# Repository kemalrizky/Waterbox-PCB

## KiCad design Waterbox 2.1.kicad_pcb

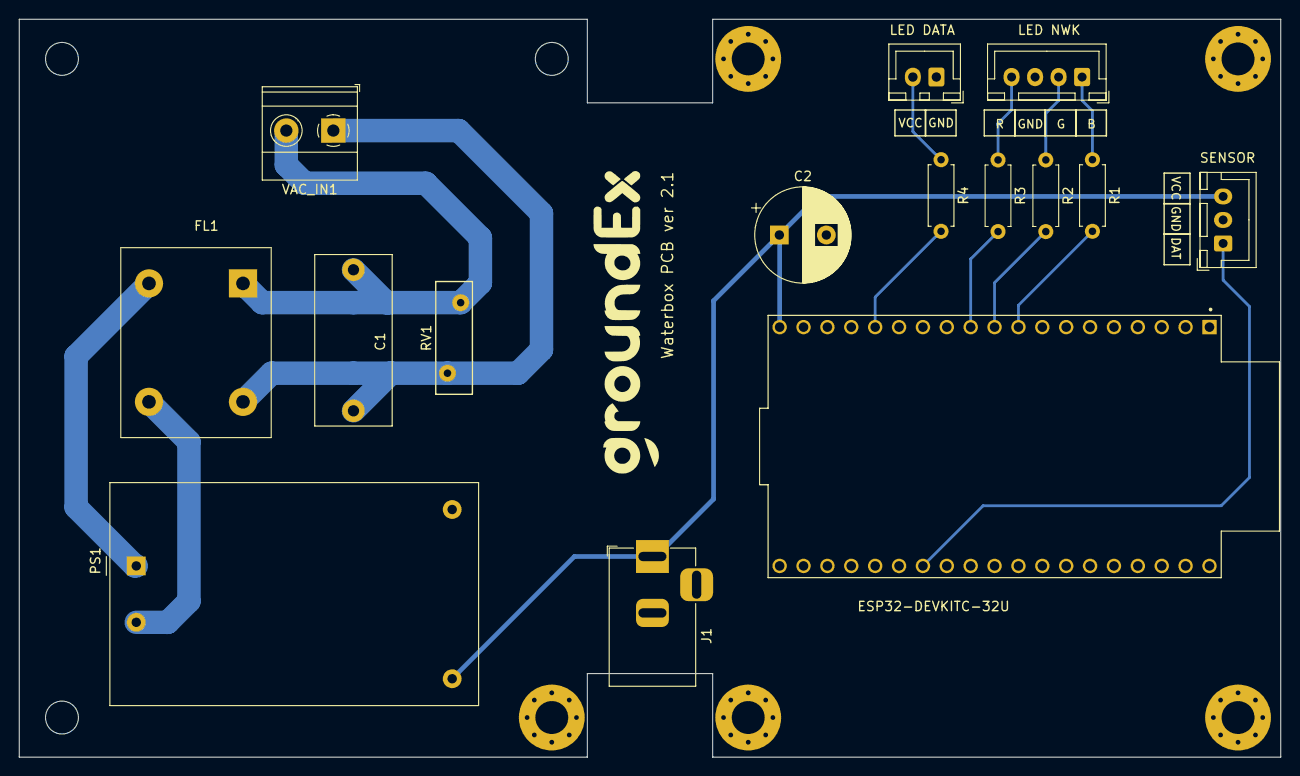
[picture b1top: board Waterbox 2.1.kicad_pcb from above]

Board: 2 copper layers, 134.2 x 78.5 mm, 23 parts (0 on the bottom side), 15 nets.

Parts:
C1: 0.1 uF / 275 V; C_Rect_L18.0mm_W8.0mm_P15.00mm_FKS3_FKP3
C2: 220 uF; CP_Radial_D10.0mm_P5.00mm
ESP32-DEVKITC-32U: ESP32-DEVKITC-32U; MODULE_ESP32-DEVKITC-32U
FL1: 10 mH; L_CommonMode_PulseElectronics_PH9455x705NL_1
H1, H2, H3: MountingHole_Pad; MountingHole_3.5mm
H4, H5, H6, H7, H8: MountingHole_Pad; MountingHole_3.5mm_Pad_Via
J1: Jack-DC; BarrelJack_Horizontal
LED DATA: LED; JST_XH_B2B-XH-A_1x02_P2.50mm_Vertical
LED NWK: LED_BGKR; JST_XH_B4B-XH-A_1x04_P2.50mm_Vertical
PS1: HLK-5M05; Converter_ACDC_HiLink_HLK-5Mxx
R1, R2, R3, R4: 330R; R_Axial_DIN0207_L6.3mm_D2.5mm_P7.62mm_Horizontal
RV1: 10D561; RV_Disc_D12mm_W3.9mm_P7.5mm
SENSOR: Conn_01x03; JST_XH_B3B-XH-A_1x03_P2.50mm_Vertical
VAC_IN1: Screw_Terminal_01x02; TerminalBlock_Phoenix_MKDS-1,5-2_1x02_P5.00mm_Horizontal

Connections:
+5V: C2.1, ESP32-DEVKITC-32U.19 (EXT_5V), J1.1, PS1.4 (+Vout), SENSOR.3
/LED_TEL: ESP32-DEVKITC-32U.15 (IO13), R4.2
/RGBLED_B: ESP32-DEVKITC-32U.9 (IO25), R1.2
/RGBLED_G: ESP32-DEVKITC-32U.10 (IO26), R2.2
/RGBLED_R: ESP32-DEVKITC-32U.11 (IO27), R3.2
/Sensor_Data: ESP32-DEVKITC-32U.26 (IO4), SENSOR.1
GND: C2.2, ESP32-DEVKITC-32U.14 (GND1), ESP32-DEVKITC-32U.32 (GND2), ESP32-DEVKITC-32U.38 (GND3), H4.1, H5.1, H6.1, H7.1, H8.1, J1.2, LED DATA.1 (K), LED NWK.3 (K), PS1.3 (-Vout), SENSOR.2
unnamed: LED NWK.1 (BA), R1.1
unnamed: LED NWK.2 (GA), R2.1
unnamed: LED NWK.4 (RA), R3.1
unnamed: LED DATA.2 (A), R4.1
unnamed: FL1.2, PS1.1 (AC/L)
unnamed: FL1.3, PS1.2 (AC/N)
unnamed: C1.2, FL1.4, RV1.2, VAC_IN1.1
unnamed: C1.1, FL1.1, RV1.1, VAC_IN1.2

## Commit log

2024-01-01 waterbox pcb ver 2.1
2024-01-03 changing clearance width to 0.254 mm
2024-01-13 route tracks in back copper, adding dc jack for additional dc power connector
